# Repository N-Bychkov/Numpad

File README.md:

## Members
Nikolay Bychkov, Mechanical Engineering Student (2028)
Nikolaybychkov@vt.edu

## Mentor
Dr. Arthur Ball
aball@vt.edu

## Current Status
Finished

## Project Overview

Numpad is a number pad/macro pad I designed from scratch. This project aimed to develop my Kicad and Onshape skills, learn more about the PCB design and build process, and gain experience designing for 3D printing. 

Here is a picture of the first prototype.

CAD render:

Schematic:

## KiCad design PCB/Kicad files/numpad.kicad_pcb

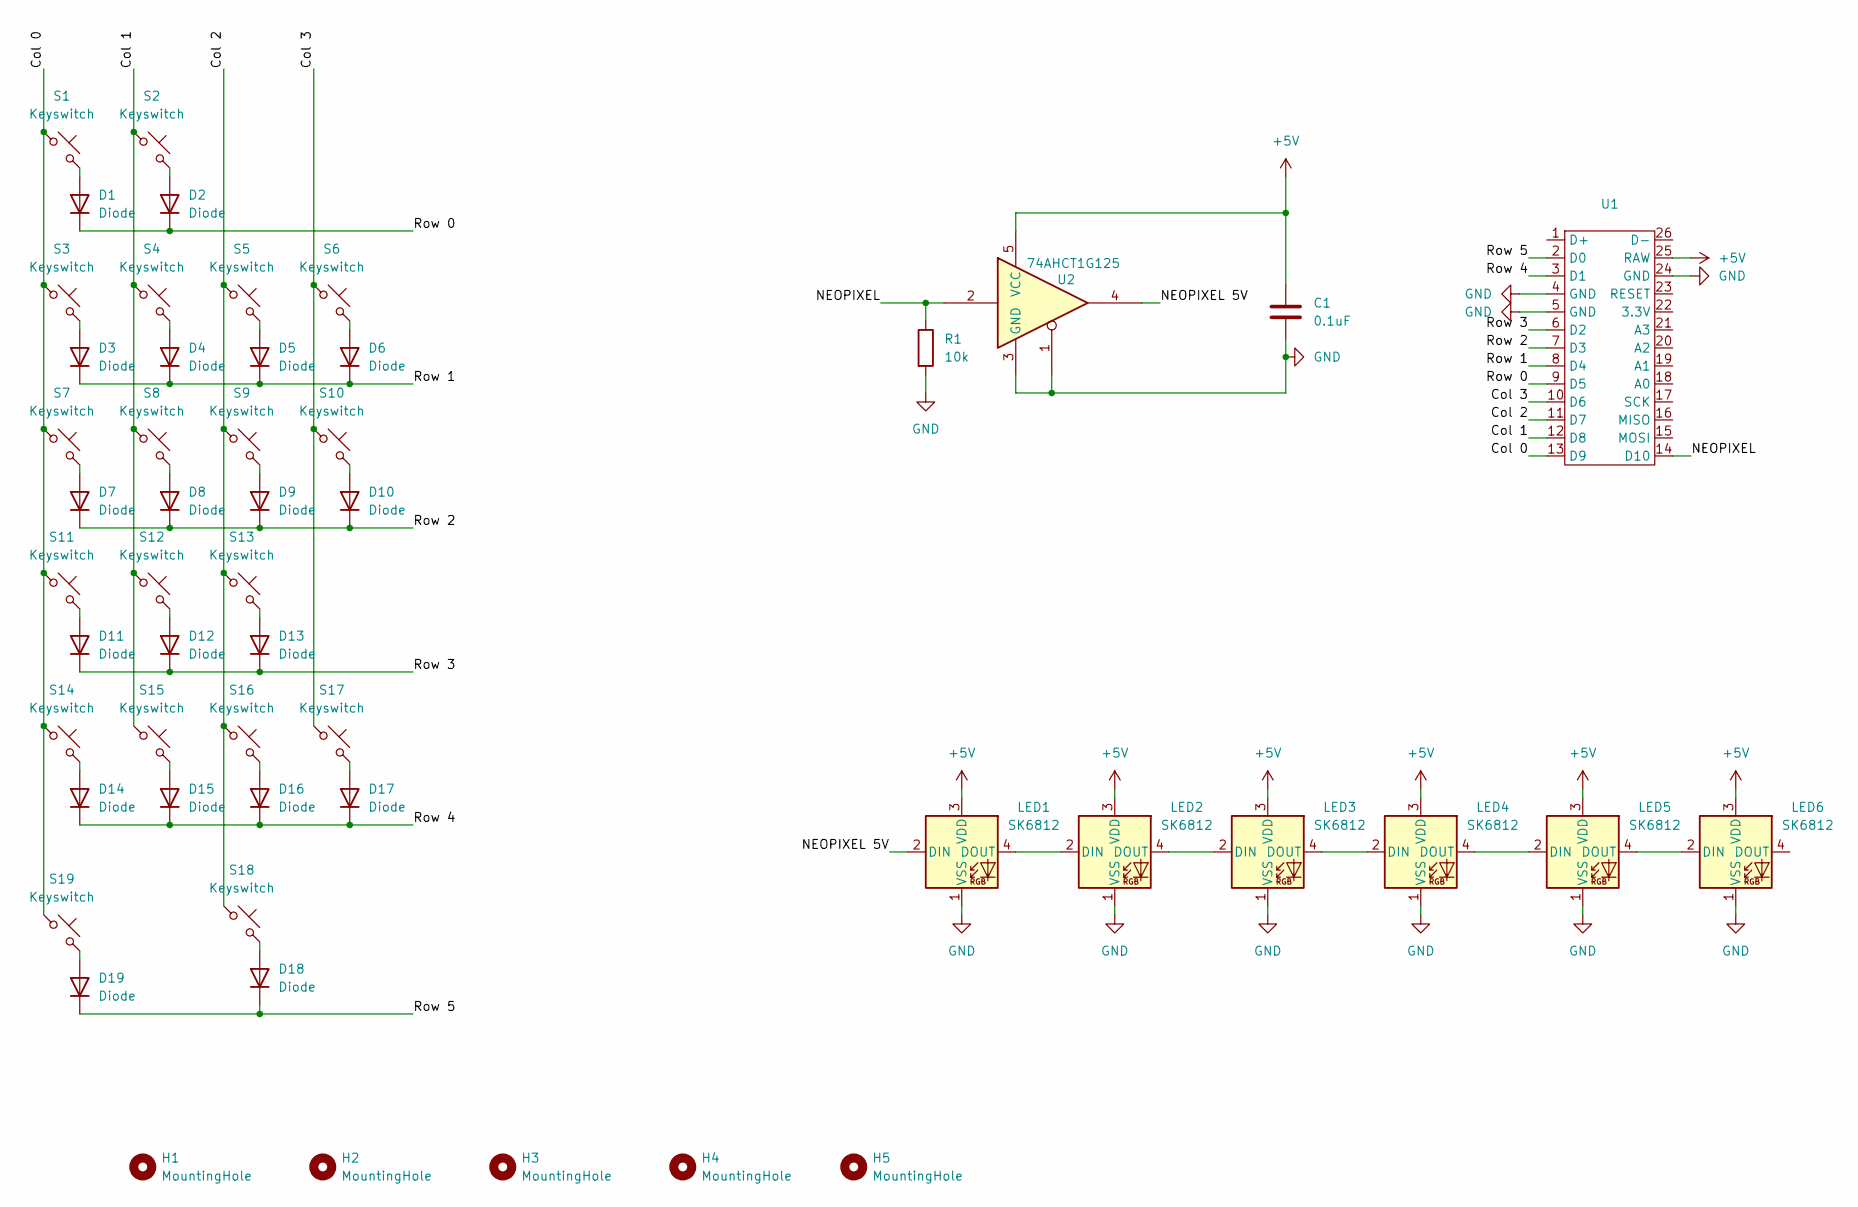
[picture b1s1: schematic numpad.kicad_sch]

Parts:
C1: 0.1uF; C_1206_3216Metric_Pad1.33x1.80mm_HandSolder
D1, D2, D3, D4, D5, D6, D7, D8, D9, D10, D11, D12, D13, D14, D15, D16, D17, D18, D19: Diode; Diode_SOD-123
H1, H2, H3, H4, H5: MountingHole; MountingHole_2.2mm_M2
LED1, LED2, LED3, LED4, LED5, LED6: SK6812; LED_SK6812_PLCC4_5.0x5.0mm_P3.2mm
R1: 10k; R_0805_2012Metric_Pad1.20x1.40mm_HandSolder
S1, S2, S3, S4, S5, S6, S7, S8, S9, S11, S12, S13, S14, S15, S16: Keyswitch; SW_Cherry_MX_1.00u_PCB
S10, S17: Keyswitch; SW_Cherry_MX_PCB_2.00u_90deg
S18: Keyswitch; SW_Cherry_MX_PCB_1.00u
S19: Keyswitch; SW_Cherry_MX_PCB_2.00u
U1: KB2040
U2: 74AHCT1G125; SOT-23-5_HandSoldering

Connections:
+5V: C1.1, LED1.3 (VDD), LED2.3 (VDD), LED3.3 (VDD), LED4.3 (VDD), LED5.3 (VDD), LED6.3 (VDD), U1.25 (RAW), U2.5 (VCC)
/Col 0: S1.1, S3.1, S7.1, S11.1, S14.1, S19.1, U1.13 (D9)
/Col 1: S2.1, S4.1, S8.1, S12.1, S15.1, U1.12 (D8)
/Col 2: S5.1, S9.1, S13.1, S16.1, S18.1, U1.11 (D7)
/Col 3: S6.1, S10.1, S17.1, U1.10 (D6)
/NEOPIXEL: R1.1, U1.14 (D10), U2.2
/NEOPIXEL 5V: LED1.2 (DIN), U2.4
/Row 0: D1.1 (K), D2.1 (K), U1.9 (D5)
/Row 1: D3.1 (K), D4.1 (K), D5.1 (K), D6.1 (K), U1.8 (D4)
/Row 2: D7.1 (K), D8.1 (K), D9.1 (K), D10.1 (K), U1.7 (D3)
/Row 3: D11.1 (K), D12.1 (K), D13.1 (K), U1.6 (D2)
/Row 4: D14.1 (K), D15.1 (K), D16.1 (K), D17.1 (K), U1.3 (D1)
/Row 5: D18.1 (K), D19.1 (K), U1.2 (D0)
GND: C1.2, LED1.1 (VSS), LED2.1 (VSS), LED3.1 (VSS), LED4.1 (VSS), LED5.1 (VSS), LED6.1 (VSS), R1.2, U1.4 (GND), U1.5 (GND), U1.24 (GND), U2.1, U2.3 (GND)
unnamed: D1.2 (A), S1.2
unnamed: D2.2 (A), S2.2
unnamed: D3.2 (A), S3.2
unnamed: D4.2 (A), S4.2
unnamed: D5.2 (A), S5.2
unnamed: D6.2 (A), S6.2
unnamed: D7.2 (A), S7.2
unnamed: D8.2 (A), S8.2
unnamed: D9.2 (A), S9.2
unnamed: D10.2 (A), S10.2
unnamed: D11.2 (A), S11.2
unnamed: D12.2 (A), S12.2
unnamed: D13.2 (A), S13.2
unnamed: D14.2 (A), S14.2
unnamed: D15.2 (A), S15.2
unnamed: D16.2 (A), S16.2
unnamed: D17.2 (A), S17.2
unnamed: D18.2 (A), S18.2
unnamed: D19.2 (A), S19.2
unnamed: LED1.4 (DOUT), LED2.2 (DIN)
unnamed: LED2.4 (DOUT), LED3.2 (DIN)
unnamed: LED3.4 (DOUT), LED4.2 (DIN)
unnamed: LED4.4 (DOUT), LED5.2 (DIN)
unnamed: LED5.4 (DOUT), LED6.2 (DIN)

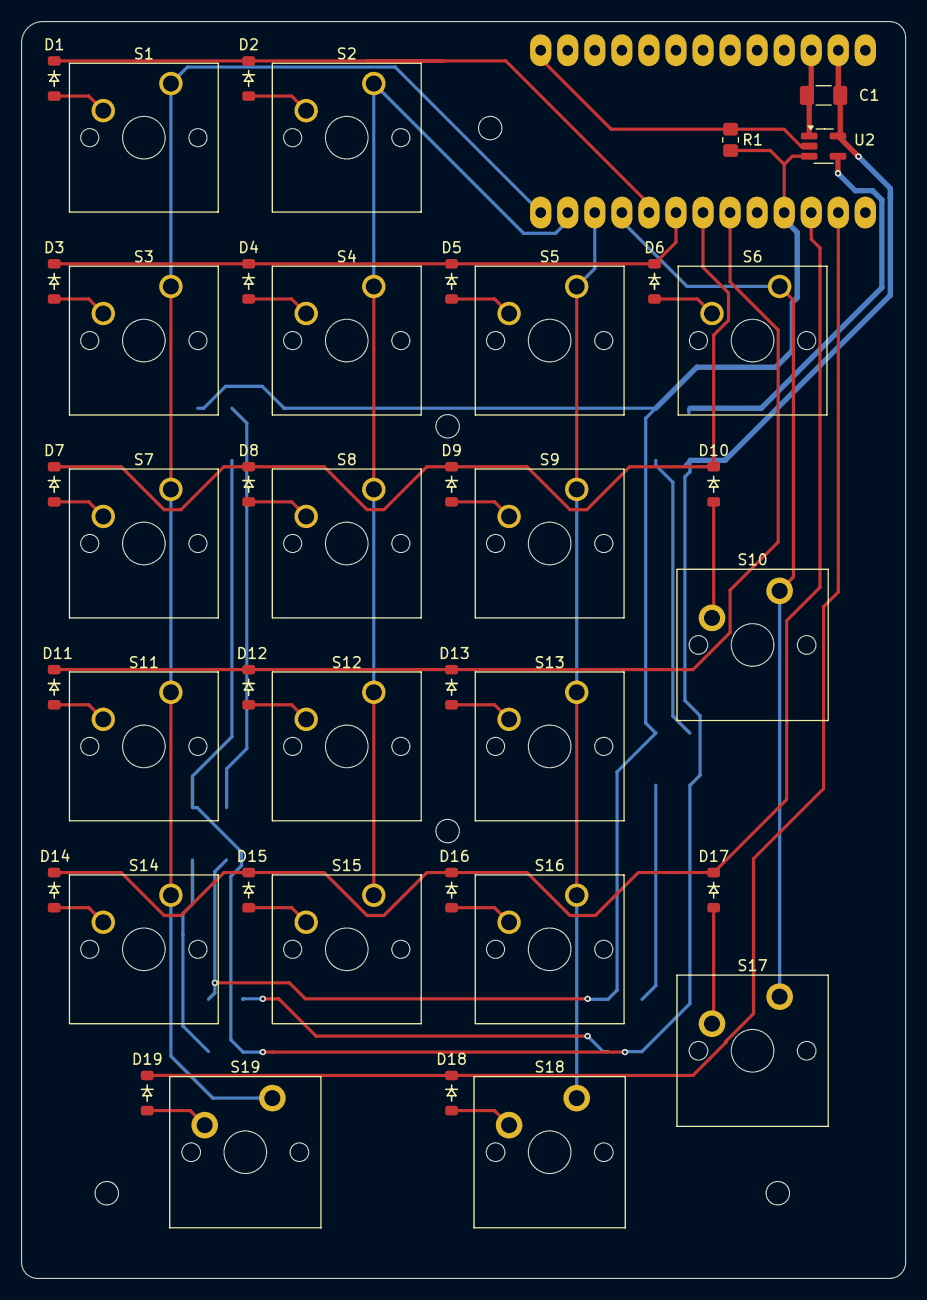
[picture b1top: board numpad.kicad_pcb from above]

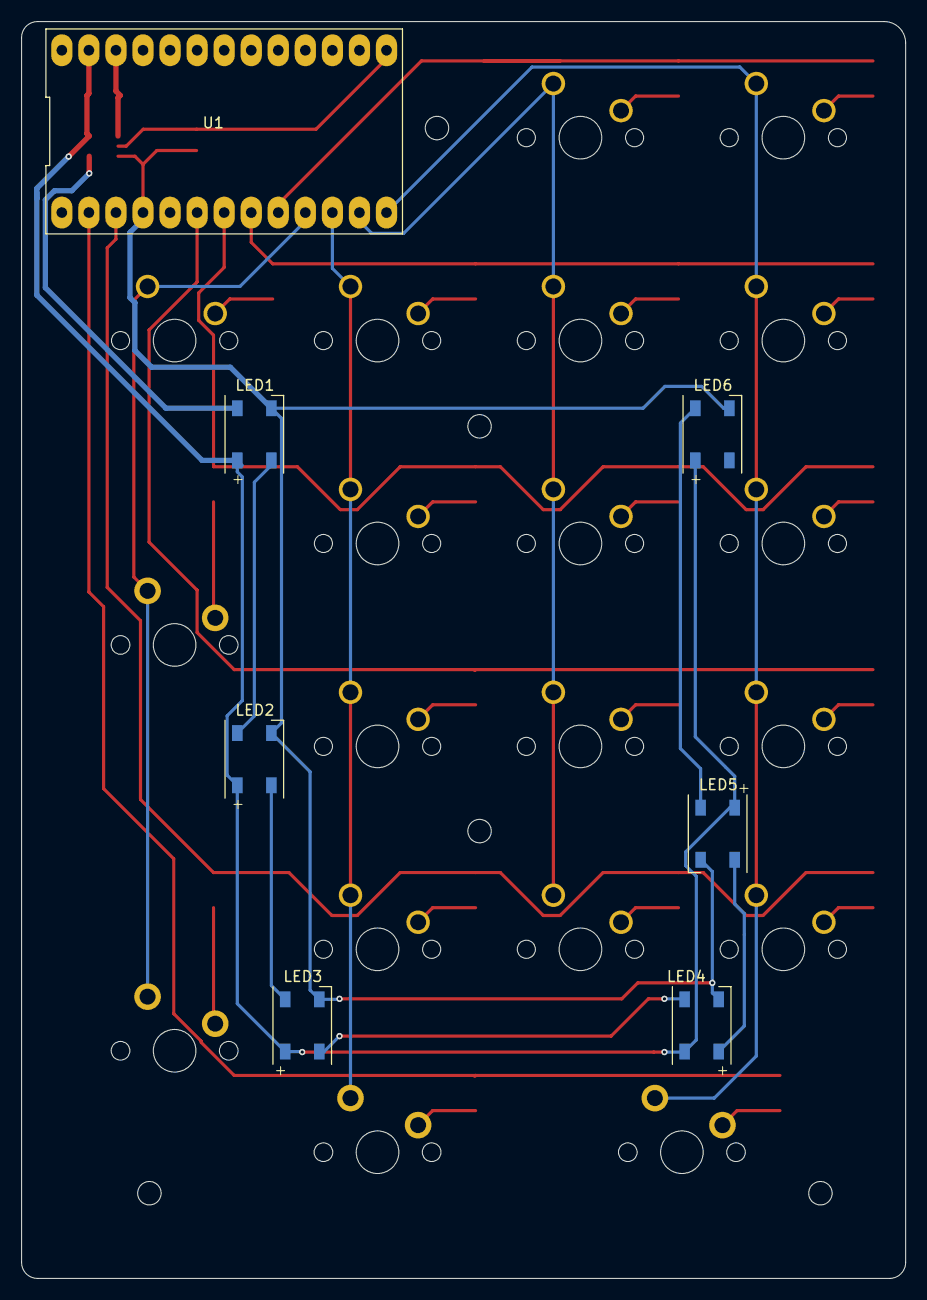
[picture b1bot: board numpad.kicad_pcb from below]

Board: 2 copper layers, 83.0 x 118.0 mm, 53 parts (7 on the bottom side), 38 nets.

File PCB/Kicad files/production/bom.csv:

Designator,Footprint,Quantity,Value,LCSC Part #
C1,1206,1,0.1uF,
"D1, D10, D11, D12, D13, D14, D15, D16, D17, D18, D19, D2, D3, D4, D5, D6, D7, D8, D9",Diode_SOD-123,19,Diode,
"LED1, LED2, LED3, LED4, LED5, LED6",LED_SK6812_PLCC4_5.0x5.0mm_P3.2mm,6,SK6812,
R1,0805,1,10k,
"S1, S11, S12, S13, S14, S15, S16, S2, S3, S4, S5, S6, S7, S8, S9",SW_Cherry_MX_1.00u_PCB,15,Keyswitch,
"S10, S17",SW_Cherry_MX_PCB_2.00u_90deg,2,Keyswitch,
S18,SW_Cherry_MX_PCB_1.00u,1,Keyswitch,
S19,SW_Cherry_MX_PCB_2.00u,1,Keyswitch,
U1,KB2040,1,~,
U2,SOT-23-5_HandSoldering,1,74AHCT1G125,

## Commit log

2024-09-04 main upload
2024-09-04 read me updates
2026-02-09 Revise README with project completion details
    Updated project status to 'Finished' and removed placeholders.
2026-02-09 Update member details and project overview in README
